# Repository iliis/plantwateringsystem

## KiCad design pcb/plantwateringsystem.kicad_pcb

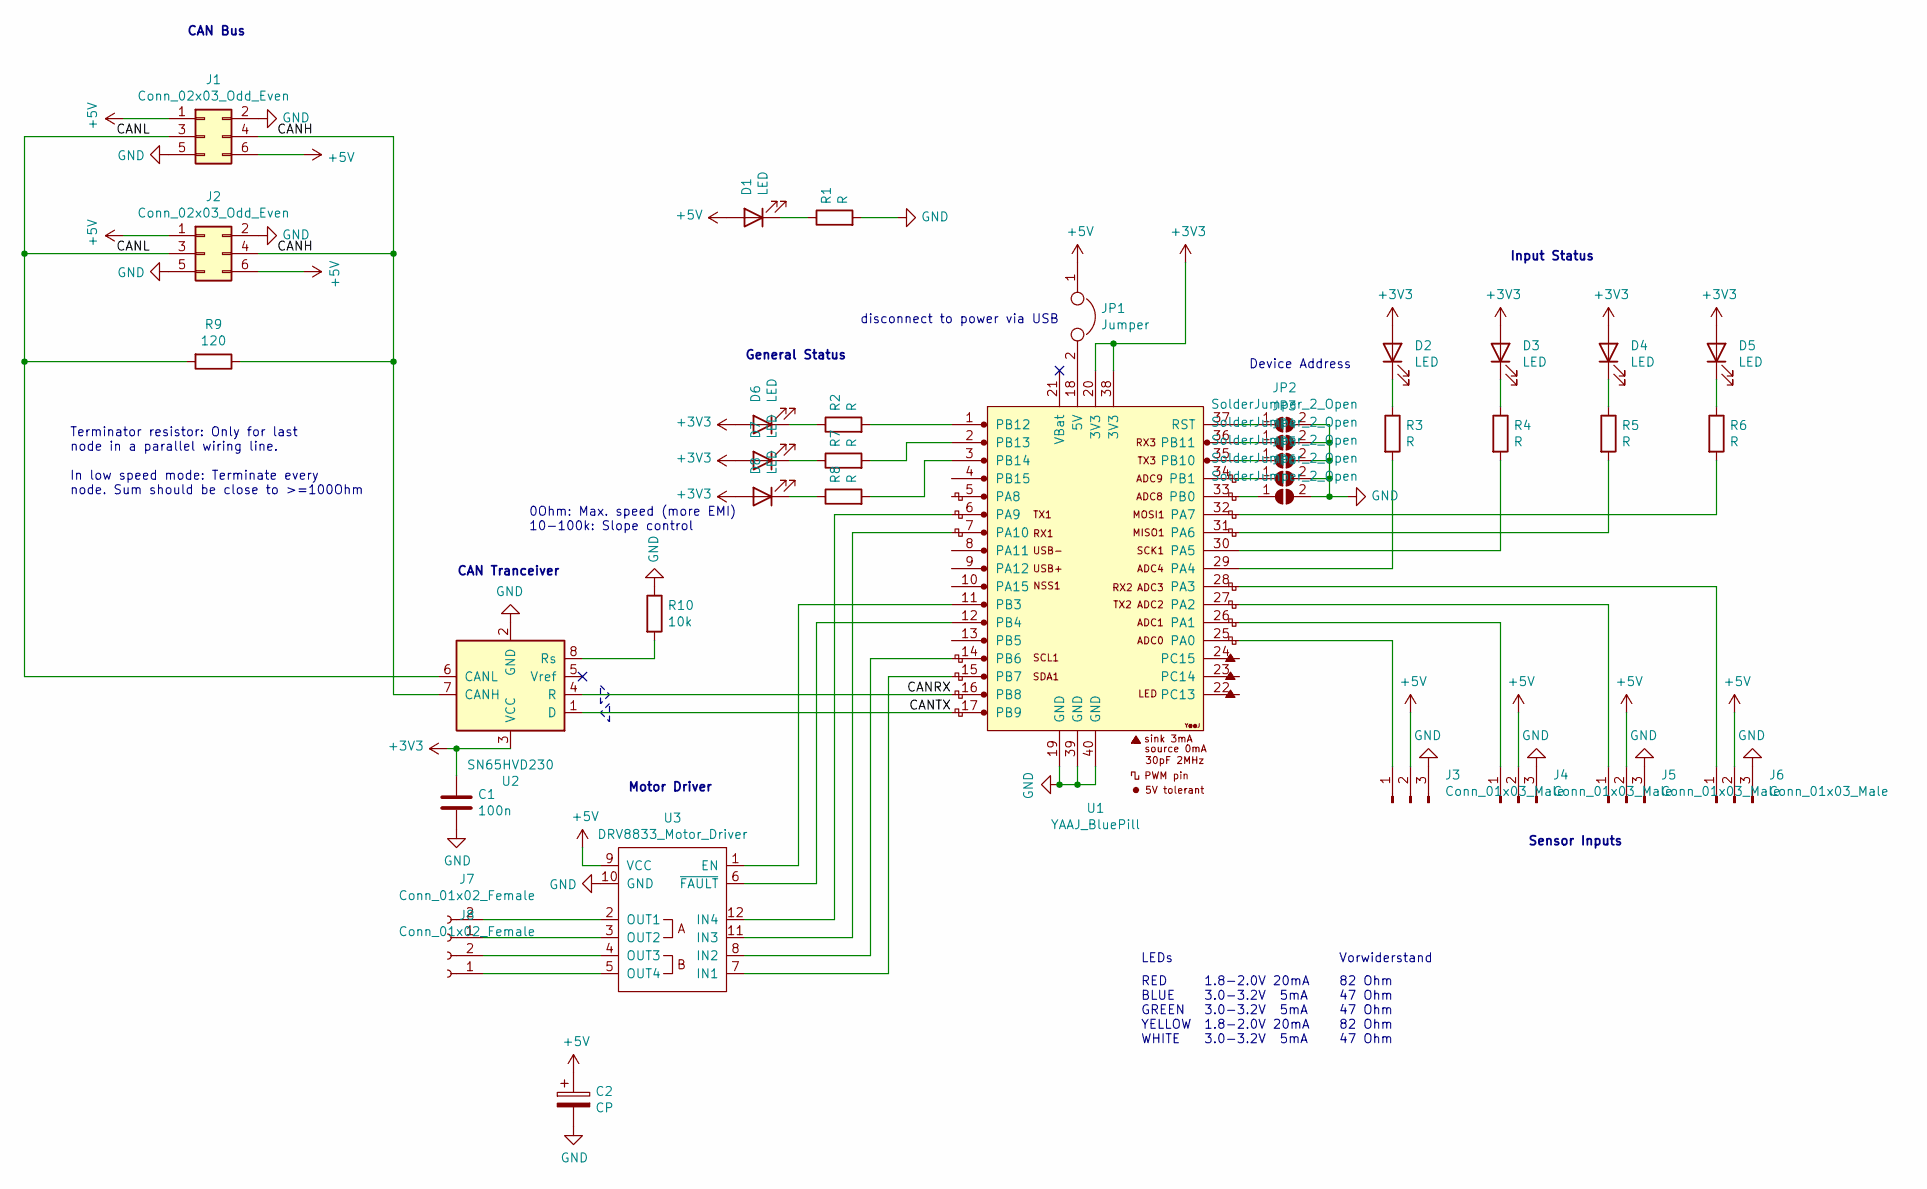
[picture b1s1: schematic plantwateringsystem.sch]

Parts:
C1: 100n; C_0805_2012Metric_Pad1.18x1.45mm_HandSolder
C2: CP; CP_Radial_D8.0mm_P3.80mm
D1, D2, D3, D4, D5, D6, D7, D8: LED; LED_0805_2012Metric_Pad1.15x1.40mm_HandSolder
J1, J2: Conn_02x03_Odd_Even; IDC-Header_2x03_P2.54mm_Vertical
J3, J4, J5, J6: Conn_01x03_Male; PinHeader_1x03_P2.54mm_Horizontal
J7, J8: Conn_01x02_Female; PinHeader_1x02_P2.54mm_Vertical
JP1: Jumper; PinHeader_1x02_P2.54mm_Vertical
JP2, JP3, JP4, JP5, JP6: SolderJumper_2_Open; SolderJumper-2_P1.3mm_Open_TrianglePad1.0x1.5mm
R1, R2, R3, R4, R5, R6, R7, R8: R; R_0805_2012Metric_Pad1.20x1.40mm_HandSolder
R9: 120; R_0805_2012Metric_Pad1.20x1.40mm_HandSolder
R10: 10k; R_0805_2012Metric_Pad1.20x1.40mm_HandSolder
U1: YAAJ_BluePill; YAAJ_BluePill_1
U2: SN65HVD230; SOIC-8_3.9x4.9mm_P1.27mm
U3: DRV8833_Motor_Driver; DRV8833_Motor_Driver_Module

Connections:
+3V3: C1.1, D2.2 (A), D3.2 (A), D4.2 (A), D5.2 (A), D6.2 (A), D7.2 (A), D8.2 (A), U1.20 (3V3), U1.38 (3V3), U2.3 (VCC)
+5V: C2.1, D1.2 (A), J1.1, J1.6, J2.1, J2.6, J3.2, J4.2, J5.2, J6.2, JP1.1, U3.9 (VCC)
/CANH: J1.4, J2.4, R9.1, U2.7 (CANH)
/CANL: J1.3, J2.3, R9.2, U2.6 (CANL)
/CANRX: U1.16 (PB8), U2.4 (R)
/CANTX: U1.17 (PB9), U2.1 (D)
GND: C1.2, C2.2, J1.2, J1.5, J2.2, J2.5, J3.3, J4.3, J5.3, J6.3, JP2.2 (B), JP3.2 (B), JP4.2 (B), JP5.2 (B), JP6.2 (B), R1.2, R10.1, U1.19 (GND), U1.39 (GND), U1.40 (GND), U2.2 (GND), U3.10 (GND)
unnamed: D1.1 (K), R1.1
unnamed: D2.1 (K), R3.1
unnamed: D3.1 (K), R4.1
unnamed: D4.1 (K), R5.1
unnamed: D5.1 (K), R6.1
unnamed: D6.1 (K), R2.1
unnamed: D7.1 (K), R7.1
unnamed: D8.1 (K), R8.1
unnamed: J3.1, U1.25 (PA0)
unnamed: J4.1, U1.26 (PA1)
unnamed: J5.1, U1.27 (PA2)
unnamed: J6.1, U1.28 (PA3)
unnamed: J7.1, U3.3 (OUT2)
unnamed: J7.2, U3.2 (OUT1)
unnamed: J8.1, U3.5 (OUT4)
unnamed: J8.2, U3.4 (OUT3)
unnamed: JP1.2, U1.18 (5V)
unnamed: JP2.1 (A), U1.37 (RST)
unnamed: JP3.1 (A), U1.36 (PB11)
unnamed: JP4.1 (A), U1.35 (PB10)
unnamed: JP5.1 (A), U1.34 (PB1)
unnamed: JP6.1 (A), U1.33 (PB0)
unnamed: R2.2, U1.1 (PB12)
unnamed: R3.2, U1.29 (PA4)
unnamed: R4.2, U1.30 (PA5)
unnamed: R5.2, U1.31 (PA6)
unnamed: R6.2, U1.32 (PA7)
unnamed: R7.2, U1.2 (PB13)
unnamed: R8.2, U1.3 (PB14)
unnamed: R10.2, U2.8 (Rs)
unnamed: U1.6 (PA9), U3.12 (IN4)
unnamed: U1.7 (PA10), U3.11 (IN3)
unnamed: U1.11 (PB3), U3.1 (EN)
unnamed: U1.12 (PB4), U3.6 (~FAULT)
unnamed: U1.14 (PB6), U3.8 (IN2)
unnamed: U1.15 (PB7), U3.7 (IN1)

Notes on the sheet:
CAN Bus
disconnect to power via USB
Terminator resistor: Only for last node in a parallel wiring line. In low speed mode: Terminate every node. Sum should be close to >=100Ohm
Device Address
Sensor Inputs
Input Status
General Status
Motor Driver
RED BLUE GREEN YELLOW WHITE
1.8-2.0V 20mA 3.0-3.2V 5mA 3.0-3.2V 5mA 1.8-2.0V 20mA 3.0-3.2V 5mA
LEDs
82 Ohm 47 Ohm 47 Ohm 82 Ohm 47 Ohm
Vorwiderstand
0Ohm: Max. speed (more EMI) 10-100k: Slope control
CAN Tranceiver

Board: 2 copper layers, 37 parts (0 on the bottom side), 43 nets, no tracks yet.

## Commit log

2021-02-14 Schema and partial layout of sensor node board.
